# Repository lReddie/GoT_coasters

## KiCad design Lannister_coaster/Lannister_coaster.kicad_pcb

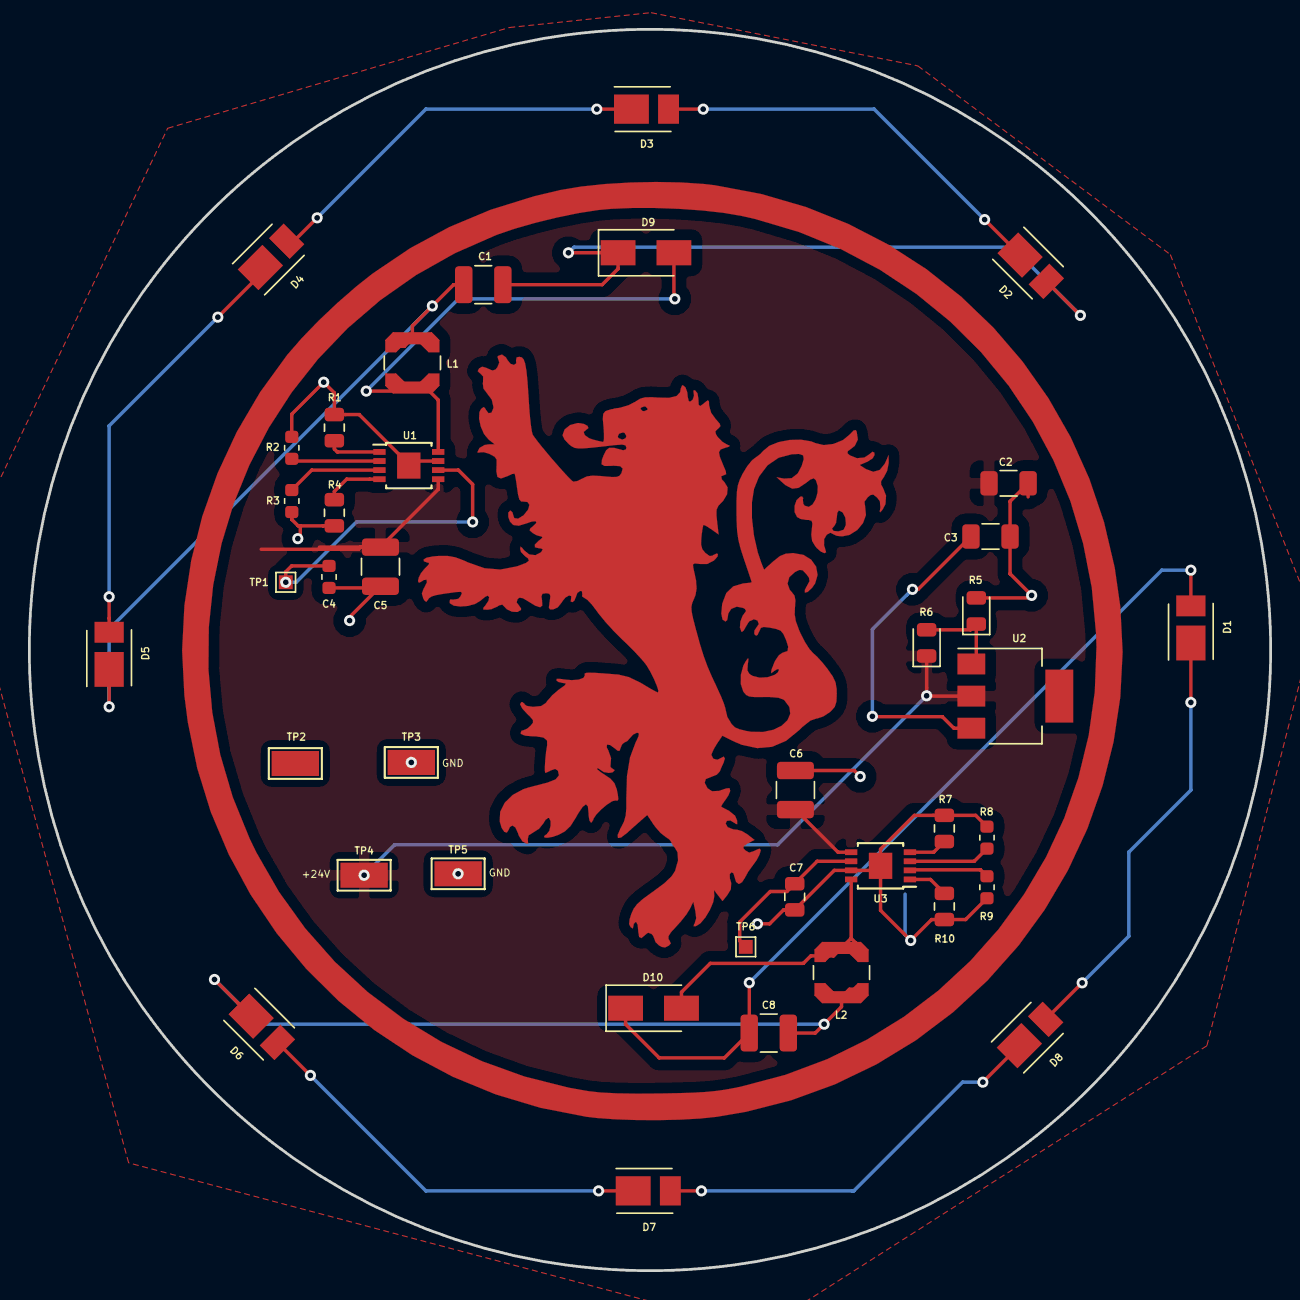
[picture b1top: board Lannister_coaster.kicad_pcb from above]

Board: 2 copper layers, 88.9 x 88.9 mm, 39 parts (0 on the bottom side), 26 nets.

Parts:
C1, C5, C6, C8: C; C_1210_3225Metric
C2, C3: CP1; C_1206_3216Metric
C4: C; C_0603_1608Metric
C7: C; C_0805_2012Metric
D1, D2, D3, D4, D5, D6, D7, D8: LED; LED_PLCC_2835_Handsoldering
D9, D10: D_Schottky; D_SMA
L1, L2: L; L_Coilcraft_LPS4018
R1, R4, R7, R10: R; R_0805_2012Metric
R2, R3, R8, R9: R; R_0603_1608Metric
R5, R6: R; LED_0805_2012Metric
TP1, TP6: TestPoint; TestPoint_Pad_1.0x1.0mm
TP2, TP3, TP4, TP5: TestPoint; TestPoint_Keystone_5015_Micro-Minature
U1, U3: LM3407MY; MSOP-8-1EP_3x3mm_P0.65mm_EP1.68x1.88mm
U2: LM317_3PinPackage; SOT-223

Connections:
+24V: C2.1, C5.1, C6.1, R6.1, TP4.1, U1.5, U2.2, U3.5
GND: C2.2, C3.2, C4.2, C5.2, C6.2, C7.2, R1.2, R2.2, R3.2, R4.2, R5.2, R7.2, R8.2, R9.2, R10.2, TP3.1, TP5.1, U1.7, U1.9, U3.7, U3.9
unnamed: C1.1, D2.2, D9.1
unnamed: C1.2, D5.1, L1.1
unnamed: C3.1, U2.3
unnamed: C4.1, TP1.1, U1.6
unnamed: C7.1, TP6.1, U3.6
unnamed: C8.1, D1.2, D10.1
unnamed: C8.2, D6.1, L2.1
unnamed: D1.1, D8.2
unnamed: D2.1, D3.2
unnamed: D3.1, D4.2
unnamed: D4.1, D5.2
unnamed: D6.2, D7.1
unnamed: D7.2, D8.1
unnamed: D9.2, L1.2, U1.8
unnamed: D10.2, L2.2, U3.8
unnamed: R1.1, U1.1
unnamed: R2.1, U1.2
unnamed: R3.1, U1.3
unnamed: R4.1, U1.4
unnamed: R5.1, R6.2, U2.1
unnamed: R7.1, U3.4
unnamed: R8.1, U3.3
unnamed: R9.1, U3.2
unnamed: R10.1, U3.1
